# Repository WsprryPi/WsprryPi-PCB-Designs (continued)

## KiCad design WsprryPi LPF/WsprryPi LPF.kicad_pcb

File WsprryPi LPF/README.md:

# WsprryPi LPF Board

A hand-assembled, seven-element low-pass filter (LPF) board with three series inductors and four shunt-capacitor positions. Each shunt position supports two parallel capacitors.

**Design status: in development; not yet qualified for production or RF use.** KiCad checks report zero DRC violations, zero unconnected items, and zero schematic-parity issues. Assembly fit and measured RF performance remain unverified.

## Project files

Open [WsprryPi LPF.kicad_pro](WsprryPi%20LPF.kicad_pro) in KiCad 10.0.1 or newer. The KiCad sources are authoritative; generate any required schematic export from the current source revision.

The [project libraries](libraries/README.md) contain every symbol and footprint used by the design, plus available 3D models. Keep the `libraries/` folder and library tables with the project; their `${KIPRJMOD}` paths resolve within this directory. Library documentation covers connector options, model limitations, sources, and licenses.

The [filter workbook](./LPF-Values.xlsx) lists standard E96/E24 values for a seven-element, 1 dB Chebyshev C-L-C ladder and its ideal, lossless 50-ohm response. Parallel E24 capacitor pairs are used where their sum better approaches the target value. The 3 dB cutoff and fundamental-loss columns are calculated from the listed installed values, not the unrounded prototype values. The board does not implement a DC-blocking capacitor.

The 2 m filter is fully specified as `47.5 pF – 60.4 nH – 68.1 pF – 63.4 nH – 68.1 pF – 60.4 nH – 47.5 pF`. Its modeled 3 dB cutoff is 148.279504 MHz and its modeled loss at the 144.4901 MHz upper WSPR edge is 0.376 dB. The row uses the 144.4899–144.4901 MHz transmit band in the [WSPR frequency list](https://www.wsprnet.org/drupal/sites/wsprnet.org/files/wspr-qrg.pdf). Only the 2 m QRSS frequency cell is blank; no 2 m QRSS operating frequency is asserted by this project.

## Assembly

The input and output connectors are hand-fitted male 1×4 headers with 2.54 mm pin pitch. The current schematic and PCB represent both headers as one component, **J1**, using the project-local paired-header footprint on the underside (B.Cu), with **33.02 mm centerline spacing**. The local symbol and footprint are named `LPF_HeaderPair_Male_2x1x04_P2.54mm_S33.02mm`; the matching BS170-board sockets use `LPF_HeaderPair_Female_2x1x04_P2.54mm_S33.02mm`. No manufacturer or purchasing part number is specified. The connector and filter components are excluded from the BOM; a default BOM export is not a complete hand-assembly purchasing list.

### Connector pinouts and QRP Labs compatibility

J1 combines the input and output header rows:

| J1 header row | Ground pads | RF pads |
| --- | --- | --- |
| Input | 1 and 4 | 2 and 3, RF_IN |
| Output | 5 and 8 | 6 and 7, RF_OUT |

These are KiCad pad numbers, not the physical position numbers used for adaptation below. Looking down onto the component side of the saved board, the input row runs **4–3–2–1** and the output row runs **8–7–6–5** from the upper board edge to the lower edge because J1 is mounted underneath.

This design was inspired by the QRP Labs method of interchangeable plug-in LPFs, but it uses a **different pinout and is not directly compatible with QRP Labs LPFs**. The WsprryPi pinout groups the two RF contacts in the middle and brackets them with signal ground contacts. It was created to allow a denser signal path with nearby ground returns, with the intent of improving RF performance; that benefit has not yet been established by measurements on this board.

The diagram numbers **physical positions 1–4 from top to bottom**, independently of KiCad pad numbering. Both header rows have the illustrated pattern. QRP Labs uses RF–RF–GND–GND in the illustrated orientation, while WsprryPi uses GND–RF–RF–GND. See the [QRP Labs assembly drawing, page 3](https://qrp-labs.com/images/lpfkit/assembly_A4.pdf).

For the orientation shown, an operator may remove pins at **physical positions 1 and 3 from both headers of the module being adapted—four pins total**. The remaining positions **2 and 4 provide RF and ground**, respectively. This applies electrically to adapting a WsprryPi module to a QRP Labs socket or a QRP Labs module to a WsprryPi socket, provided the mechanical spacing and fit match. The WsprryPi paired header uses 33.02 mm spacing.

**Orientation matters:** turning the module end-for-end reverses both rows and changes which positions conflict. The WsprryPi GND–RF–RF–GND pinout and symmetric filter topology permit electrical connection in either direction in a matching WsprryPi socket. The cross-compatible two-contact arrangement is orientation-specific: after modification, use only the orientation shown for the adapted target socket. This is especially important because the unmodified outline alone does not establish a safe orientation.

A modified module has two empty positions in each header. It can still be electrically compatible with a socket using that module's native pinout. A WsprryPi socket has the symmetric GND–RF–RF–GND pattern, so a modified WsprryPi module can retain electrical compatibility in either native orientation. Removing pins reduces ground contacts and mechanical support. Confirm physical alignment and RF/ground contact mapping before applying RF. Adapter operation and the resulting RF response have not been physically verified.

### Toroid assembly

Core material, core size, and turn counts for L2, L4, and L6 remain unspecified in the KiCad design. Select and record them for the required inductance and intended operating band before winding.

Use **28 AWG enameled copper magnet wire (approximately 0.32 mm bare diameter)** as a provisional planning assumption, not an all-band or power-qualified requirement. The inductor footprint has **0.8 mm lead holes**. Strip the enamel from the lead portions, tin them, and mount the wound toroid upright as intended by the footprint.

Each winding has two ends: fit one end into **one pad numbered 1** and the other into **one pad numbered 2**. The footprint provides two alternative holes for each pad number; these are mounting choices, not four separate winding terminals. Do not put both winding ends into holes with the same pad number. Each pass through the core center counts as one turn.

Check the complete wound diameter, thickness, and height—including enamel, overlapping turns, lead bends, and any support or adhesive—against adjacent capacitors, inductors, board edges, and the mounting arrangement. LF windings may require multiple layers. The generic axial-inductor 3D model does not represent the finished toroid or prove clearance. Record the core, turns, wire size, measured inductance, and assembled dimensions for each filter.

### Capacitor population and lead spacing

Each of the four shunt-capacitor poles (`CA7/CB7`, `CA3/CB3`, `CA5/CB5`, and `CA1/CB1`) provides two electrically parallel footprints. Each individual footprint retains 2.50 mm lead spacing. A workbook entry written as `A + B` means that both listed capacitors are installed, one in each footprint; their order is electrically irrelevant.

For a single capacitor, there are two mounting options:

- **2.50 mm leads:** use pads 1 and 2 of either `CA` or `CB`, leaving the other footprint available for measured tuning.
- **5.00 mm leads:** span the pair, using ground pad 1 of `CA` and signal pad 2 of `CB`, or ground pad 1 of `CB` and signal pad 2 of `CA`. Both combinations provide 5.00 mm between hole centers at every pole. Do not use the two signal pads or the two ground pads together; those pairs connect to the same net.

The 5 mm option uses the existing holes and allows one wider-pitch capacitor to occupy the combined pair area. Treat both footprints as occupied by that capacitor unless a separate body-clearance check establishes room for an additional tuning part. Lead spacing alone does not establish body fit: check the selected capacitor's length, thickness, lead diameter, and clearance to the wound inductors and board edges. Record the installed capacitance, part numbers, and mounting option for each assembled filter.

### Space between filter elements

L4 and the inner capacitor pairs are centered, with space distributed between the four inductor/capacitor groups and clearance above and below L4. The following nominal gaps were measured between the existing footprint courtyards in the saved PCB on 2026-10-03:

| Adjacent elements | Courtyard gap |
| --- | ---: |
| End capacitor pair `CA1/CB1` to L2 | 0.81 mm |
| L2 to L4 | 0.66 mm |
| L4 to L6 | 0.69 mm |
| L6 to end capacitor pair `CA7/CB7` | 0.80 mm |
| Upper capacitor pair `CA3/CB3` to L4 | 0.87 mm |
| L4 to lower capacitor pair `CA5/CB5` | 0.91 mm |

These gaps distribute room for capacitor bodies and inductor windings while preserving the 5 mm capacitor mounting option. They are distances between footprint courtyards, not guaranteed clearances between assembled components. The capacitor footprints and generic inductor visualization do not describe every candidate body or wound toroid. Check the complete wound dimensions, including multilayer windings for LF filters, before selecting parts or producing manufacturing files. The paired header has 33.02 mm centerline spacing and 2.54 mm pin pitch.

The toroid model is a generic axial-inductor visualization. Check the wound component dimensions against the footprint before assembly.

## Validation

The saved design was checked on **2026-10-03 with KiCad 10.0.6**:

- **DRC:** zero violations and zero unconnected items, including a check with in-memory zone refill.
- **Schematic parity:** zero issues.
- **ERC:** no active violations; two explicitly excluded four-way-junction warnings remain visible. No ERC or DRC rule severity is set to `ignore`.
- **Libraries:** all placed symbols, footprints, and referenced STEP models resolve within the project-local library. All five symbols export successfully and all three footprints load successfully.
- **Vias:** 62 ground vias, each with a 0.6 mm pad and 0.3 mm drill; their centers lie within the saved ground fills on both copper layers.
- **Assembly documentation:** capacitor mounting options, courtyard gaps, and the paired-header geometry were checked against the saved sources and visual exports. The toroid's generic 3D model does not establish wound-component clearance.
- **BOM:** the connector and filter components are excluded from the BOM; a default export is not a complete hand-assembly purchasing list.

The title-block revision is `1.0.2`. The schematic identifies `RF_IN` as the electrical input; a `PWR_FLAG` documents externally supplied ground.

These checks do not establish assembly fit or electrical/RF performance. Treat the design as untested until revision-specific physical validation is documented. Re-run ERC and DRC with schematic parity after design changes and before producing manufacturing files. See the [repository conventions](../README.md) and [validation requirements](../CONTRIBUTING.md).

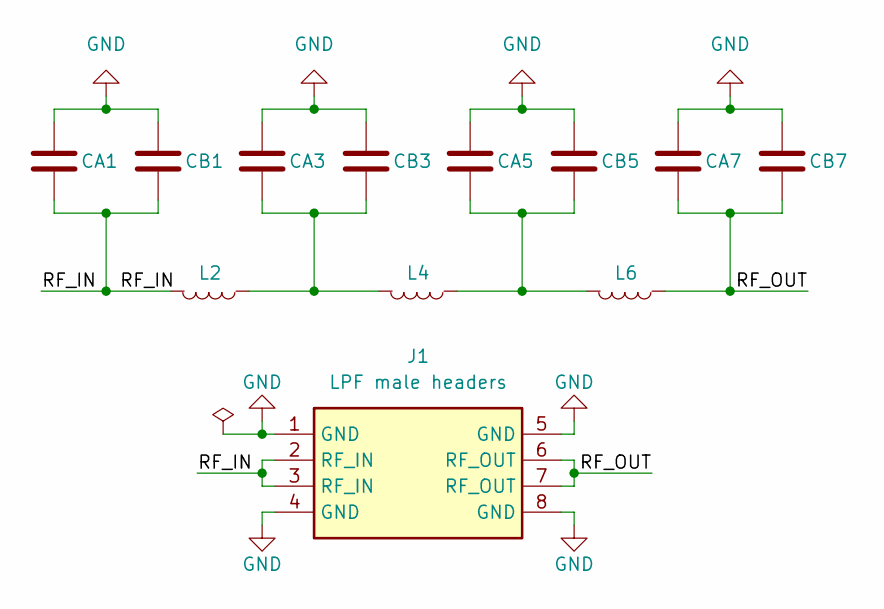
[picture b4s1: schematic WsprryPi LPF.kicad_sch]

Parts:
CA1, CA3, CA5, CA7: C; C_Disc_D3.0mm_W1.6mm_P2.50mm
CB1, CB3, CB5, CB7: C; C_Disc_D3.0mm_W1.6mm_P2.50mm
J1: LPF male headers; LPF_HeaderPair_Male_2x1x04_P2.54mm_S33.02mm
L2, L4, L6: L; L_Axial_Horiz_Torroid_Vert_12mm_D5mm_P10.2mm

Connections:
/RF_IN: CA1.2, CB1.2, J1.2 (RF_IN), J1.3 (RF_IN), L2.2
/RF_OUT: CA7.2, CB7.2, J1.6 (RF_OUT), J1.7 (RF_OUT), L6.1
GND: CA1.1, CA3.1, CA5.1, CA7.1, CB1.1, CB3.1, CB5.1, CB7.1, J1.1 (GND), J1.4 (GND), J1.5 (GND), J1.8 (GND)
unnamed: CA3.2, CB3.2, L2.1, L4.2
unnamed: CA5.2, CB5.2, L4.1, L6.2

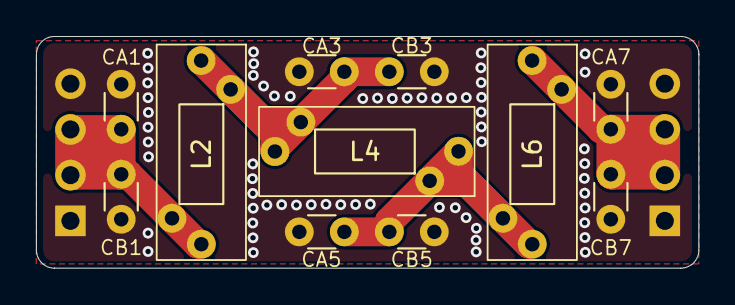
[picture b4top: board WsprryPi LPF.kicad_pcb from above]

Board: 2 copper layers, 36.8 x 12.9 mm, 12 parts (1 on the bottom side), 5 nets.
